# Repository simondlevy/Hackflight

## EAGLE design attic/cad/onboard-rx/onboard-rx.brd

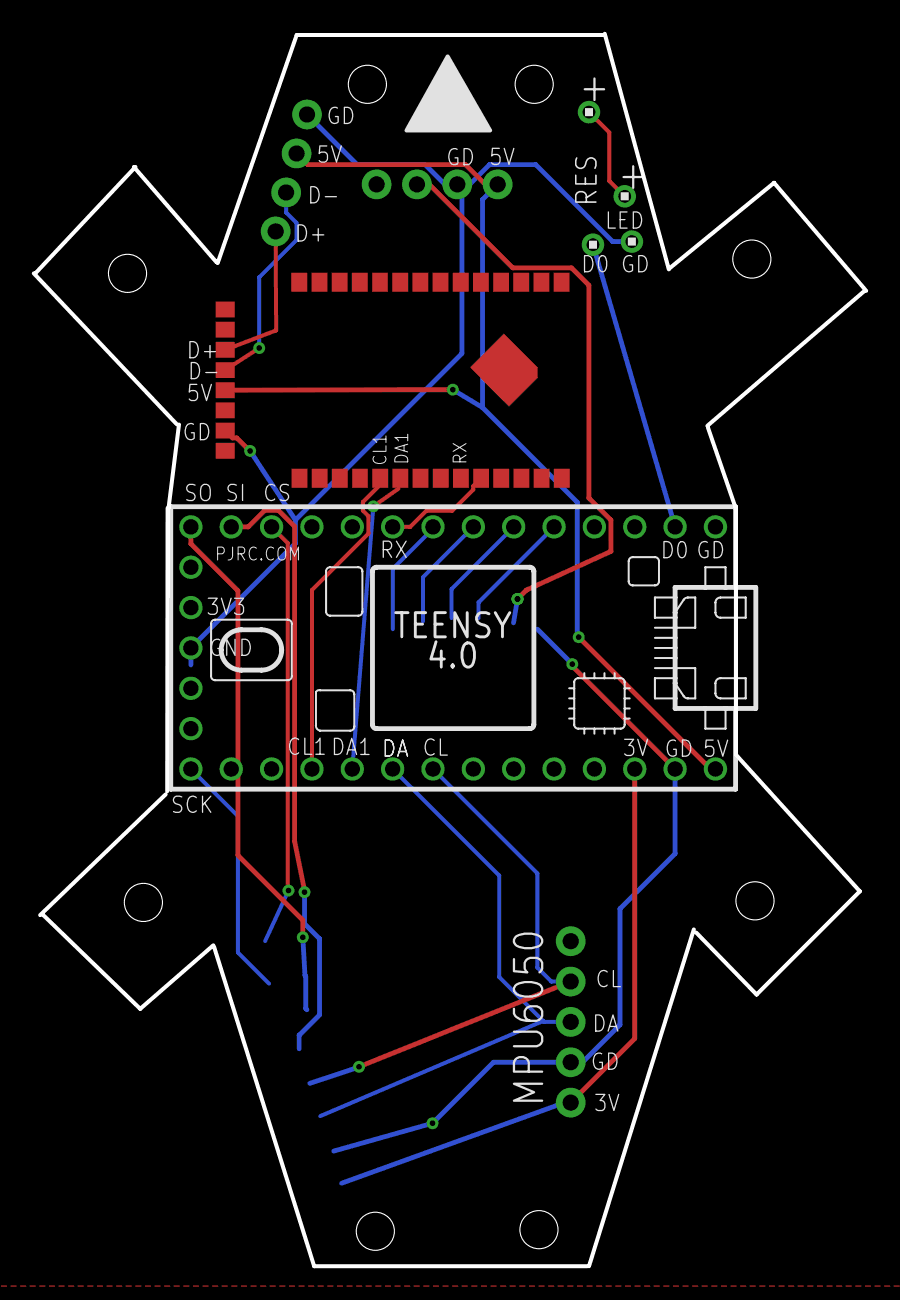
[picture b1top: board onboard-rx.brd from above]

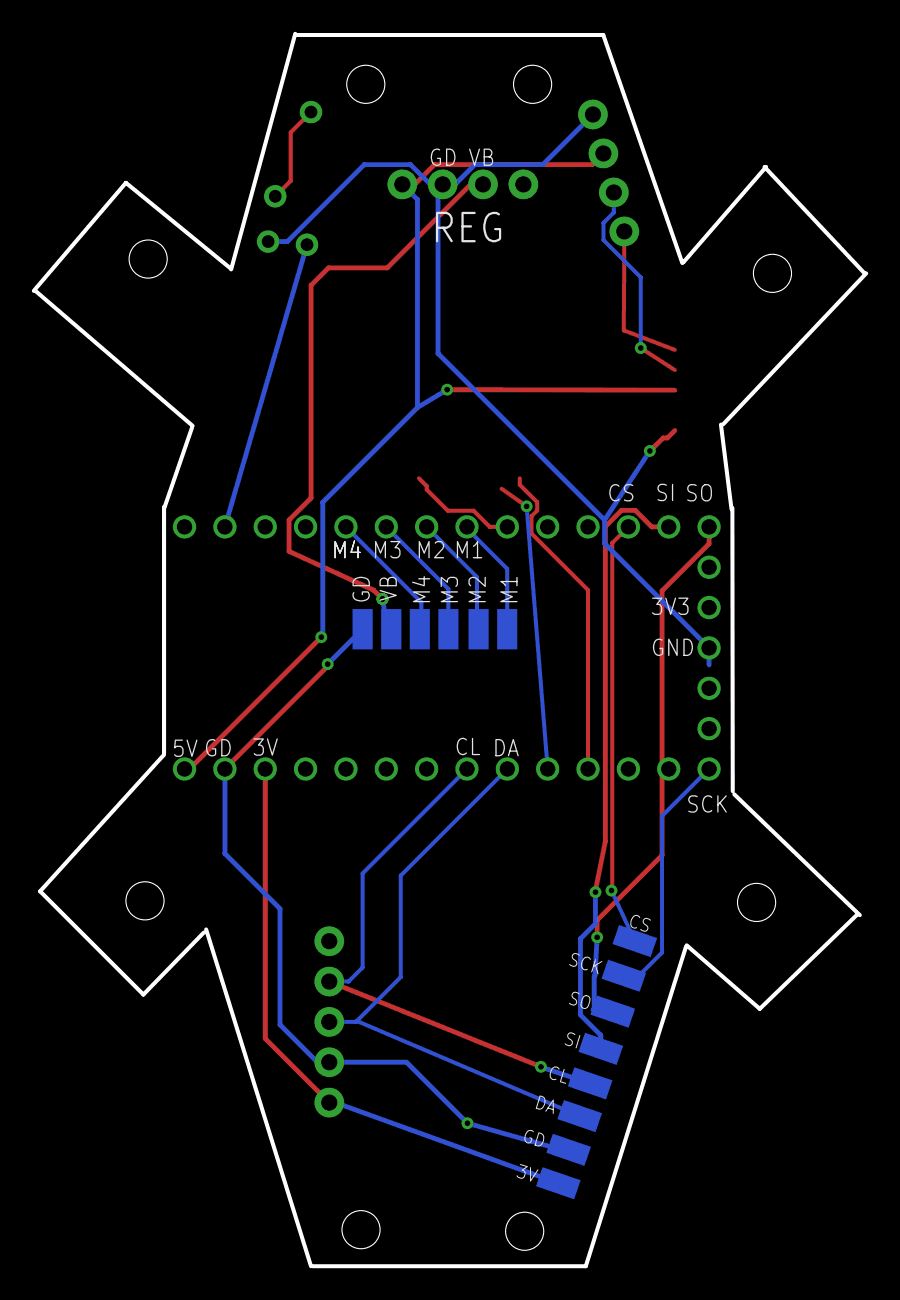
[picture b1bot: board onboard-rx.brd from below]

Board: 2 copper layers, 52.4 x 77.6 mm, 23 parts (14 on the bottom side), 21 nets.

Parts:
3V2, 3V3: SMD1,27-2,54
CS: SMD1,27-2,54
GD1, GD2: SMD1,27-2,54
GND: SMD1,27-2,54
J1: 1X05_NO_SILK
J2: 1X04_NO_SILK
M1, M2, M3, M4: SMD1,27-2,54
REG: 1X04_NO_SILK
RX1, RX2: SMD1,27-2,54
SCK: SMD1,27-2,54
U$1: TEENSY_4.0
U$2: TINYPICO-NANO-CONNECTOR
U$3, U$4, U$6, U$7: 1X1
VBAT: SMD1,27-2,54

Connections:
3V3: 3V2.1, J1.1, U$1.3V3_LO, U$2.3V3
5V: J2.2, REG.1, U$1.VIN, U$2.5V
CS: CS.1, U$1.10/CS
D+: J2.4, U$2.D+
D-: J2.3, U$2.D-
GND: GD1.1, GND.1, J1.2, J2.1, REG.2, U$1.GND2, U$1.GND3, U$2.GND$1, U$2.GND$2, U$2.GND$3, U$2.GND$4, U$7.1
LED_R_IN: U$1.0/RX, U$3.1
LED_R_OUT: U$4.1, U$6.1
M1: M1.1, U$1.6
M2: M2.1, U$1.5
M3: M3.1, U$1.4/CANRX
M4: M4.1, U$1.3/CANTX
MISO: 3V3.1, U$1.12/MISO
MOSI: RX2.1, U$1.11/MOSI
RX: U$1.7, U$2.TX
SCK: SCK.1, U$1.13/SCK
SCL: GD2.1, J1.4, U$1.19/A5/SCL
SCL1: U$1.16/A2, U$2.IO22
SDA: J1.3, RX1.1, U$1.18/A4/SDA
SDA1: U$1.17/A3, U$2.IO21
VB: REG.3, U$2.VBAT, VBAT.1

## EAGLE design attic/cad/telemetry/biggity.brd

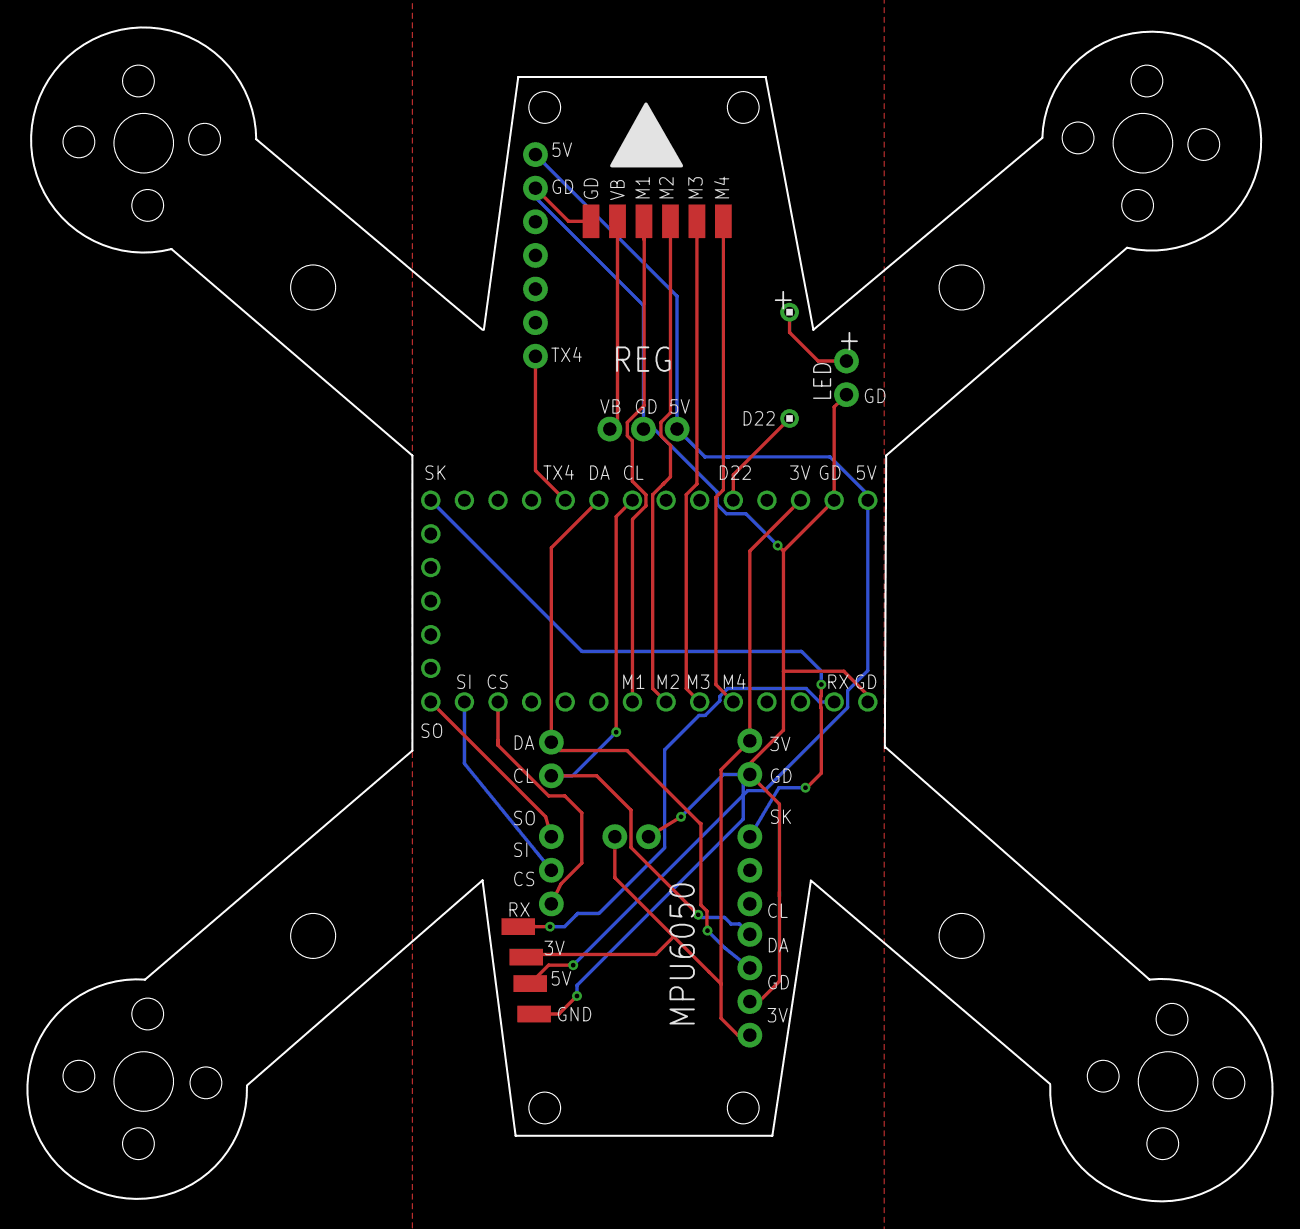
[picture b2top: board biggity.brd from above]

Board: 2 copper layers, 94.1 x 88.7 mm, 22 parts (1 on the bottom side), 18 nets.

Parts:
3V, 5V: SMD1,27-2,54
GND: SMD1,27-2,54
LED: 1X02_NO_SILK
LED_R_IN: 1X1
LED_R_OUT: 1X1
MPU6050: 1X04_NO_SILK
PAD1, PAD2, PAD3, PAD4, PAD5, PAD6: SMD1,27-2,54
PMW3901_1, PMW3901_2: 1X03_NO_SILK
PMW3901_3: 1X02_NO_SILK
REG: 1X03_NO_SILK
RX: SMD1,27-2,54
U$1: TEENSY_4.0
VL53L1_1, VL53L1_2: 1X02_NO_SILK
XIAO_ESP32C6: 1X07_NO_SILK

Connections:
3V3: 3V.1, MPU6050.1, PMW3901_3.1, U$1.3V3_LO, VL53L1_1.2
5V: 5V.1, REG.1, U$1.VIN, XIAO_ESP32C6.7
CS: PMW3901_2.3, U$1.10/CS
GND: GND.1, LED.1, MPU6050.2, PAD1.1, PMW3901_3.2, REG.2, U$1.GND, U$1.GND2, VL53L1_1.1, XIAO_ESP32C6.6
LED_R_IN: LED_R_IN.1, U$1.22/A8
LED_R_OUT: LED.2, LED_R_OUT.1
M1: PAD3.1, U$1.6
M2: PAD4.1, U$1.5
M3: PAD5.1, U$1.4/CANRX
M4: PAD6.1, U$1.3/CANTX
MISO: PMW3901_2.1, U$1.12/MISO
MOSI: PMW3901_2.2, U$1.11/MOSI
RX: RX.1, U$1.0/RX
SCK: PMW3901_1.1, U$1.13/SCK
SCL: MPU6050.4, U$1.19/A5/SCL, VL53L1_2.1
SDA: MPU6050.3, U$1.18/A4/SDA, VL53L1_2.2
TX4: U$1.17/A3, XIAO_ESP32C6.1
VBAT: PAD2.1, REG.3

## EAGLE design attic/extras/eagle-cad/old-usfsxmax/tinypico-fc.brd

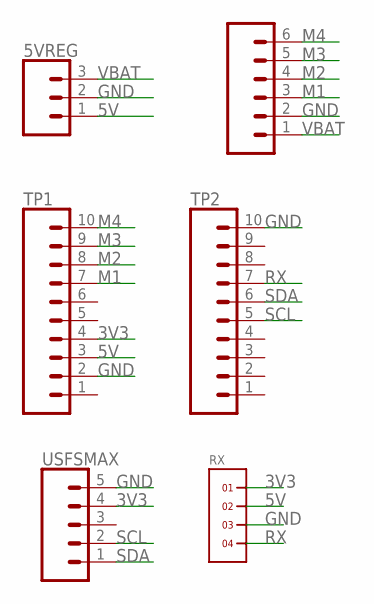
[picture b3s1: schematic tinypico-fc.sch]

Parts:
5VREG: CONN_031X03_NO_SILK; 1X03_NO_SILK
ESC: CONN_06NO_SILK_FEMALE_PTH; 1X06_NO_SILK
RX: 1X4
TP1, TP2: CONN_10NO_SILK_PTH_FEMALE; 1X10_NO_SILK
USFSMAX: CONN_05NO_SILK; 1X05_NO_SILK

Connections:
3V3: RX.1, TP1.4, USFSMAX.4
5V: 5VREG.1, RX.2, TP1.3
GND: 5VREG.2, ESC.2, RX.3, TP1.2, TP2.10, USFSMAX.5
M1: ESC.3, TP1.7
M2: ESC.4, TP1.8
M3: ESC.5, TP1.9
M4: ESC.6, TP1.10
RX: RX.4, TP2.7
SCL: TP2.5, USFSMAX.2
SDA: TP2.6, USFSMAX.1
VBAT: 5VREG.3, ESC.1

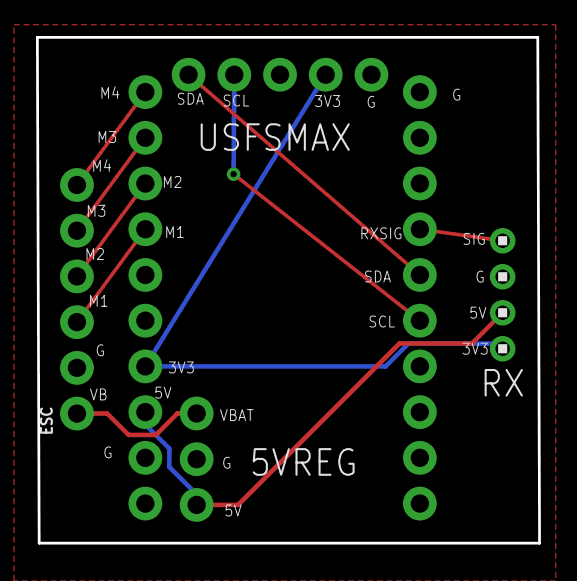
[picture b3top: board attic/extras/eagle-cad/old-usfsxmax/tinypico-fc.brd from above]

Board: 2 copper layers, 27.9 x 28.1 mm, 6 parts (0 on the bottom side), 11 nets.

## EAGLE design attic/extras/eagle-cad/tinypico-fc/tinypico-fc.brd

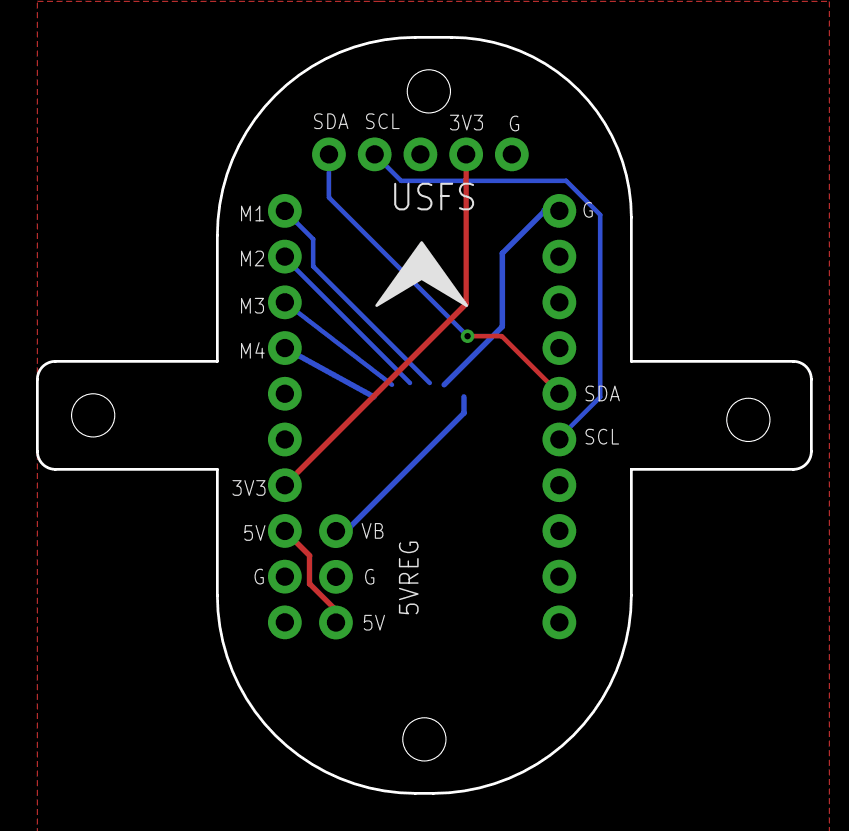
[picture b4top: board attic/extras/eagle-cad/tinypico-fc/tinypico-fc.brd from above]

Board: 2 copper layers, 43.0 x 42.0 mm, 5 parts (1 on the bottom side), 10 nets.

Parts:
5VREG: 1X03_NO_SILK
ESC: BM06B-SRSS-TB; JST-6-SMD-HORI-1.0MM
TP1, TP2: 1X10_NO_SILK
USFS: 1X05_NO_SILK

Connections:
3V3: TP1.4, USFS.4
5V: 5VREG.1, TP1.3
GND: 5VREG.2, ESC.5, TP1.2, TP2.10, USFS.5
M1: ESC.4, TP1.10
M2: ESC.3, TP1.9
M3: ESC.2, TP1.8
M4: ESC.1, TP1.7
SCL: TP2.5, USFS.2
SDA: TP2.6, USFS.1
VBAT: 5VREG.3, ESC.6

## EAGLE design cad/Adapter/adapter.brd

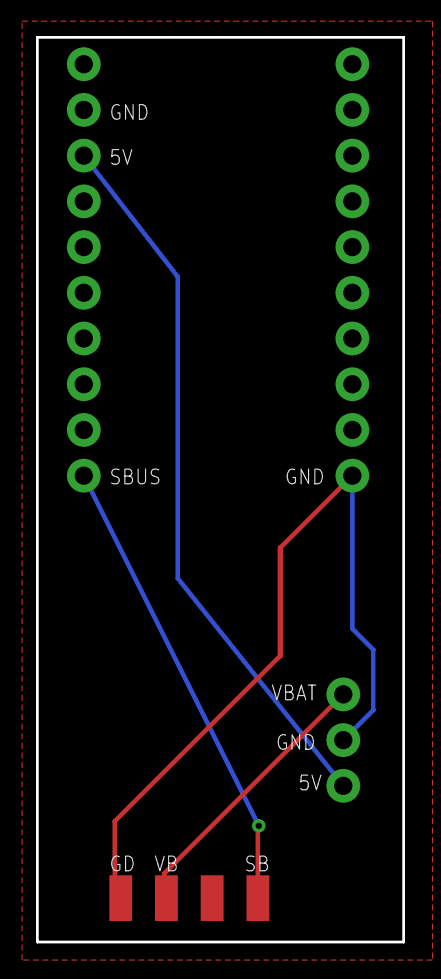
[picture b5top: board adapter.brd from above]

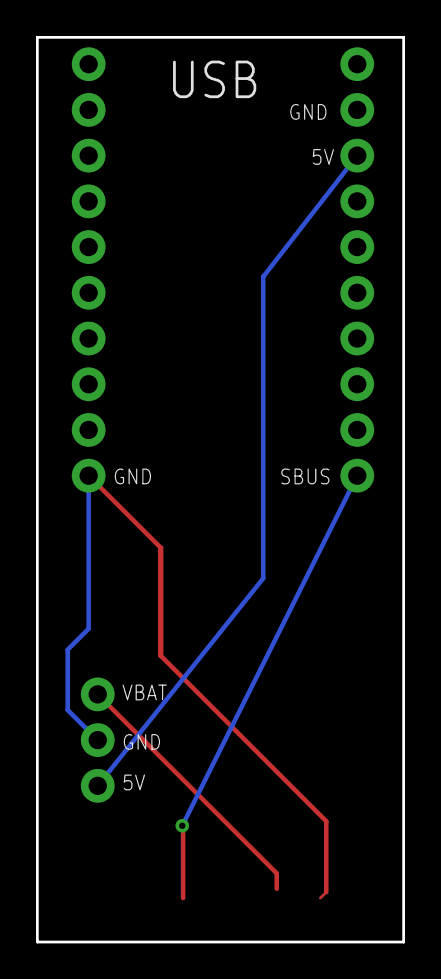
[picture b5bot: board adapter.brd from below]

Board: 2 copper layers, 20.4 x 50.3 mm, 7 parts (2 on the bottom side), 4 nets.

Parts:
GND: SMD1,27-2,54
J1, J2: 1X10_NO_SILK
J3: 1X03_NO_SILK
PAD1: SMD1,27-2,54
SBUS: SMD1,27-2,54
VBAT: SMD1,27-2,54

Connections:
5V: J2.8, J3.1
GND: GND.1, J1.1, J2.9, J3.2
SBUS: J2.1, SBUS.1
VBAT: J3.3, VBAT.1

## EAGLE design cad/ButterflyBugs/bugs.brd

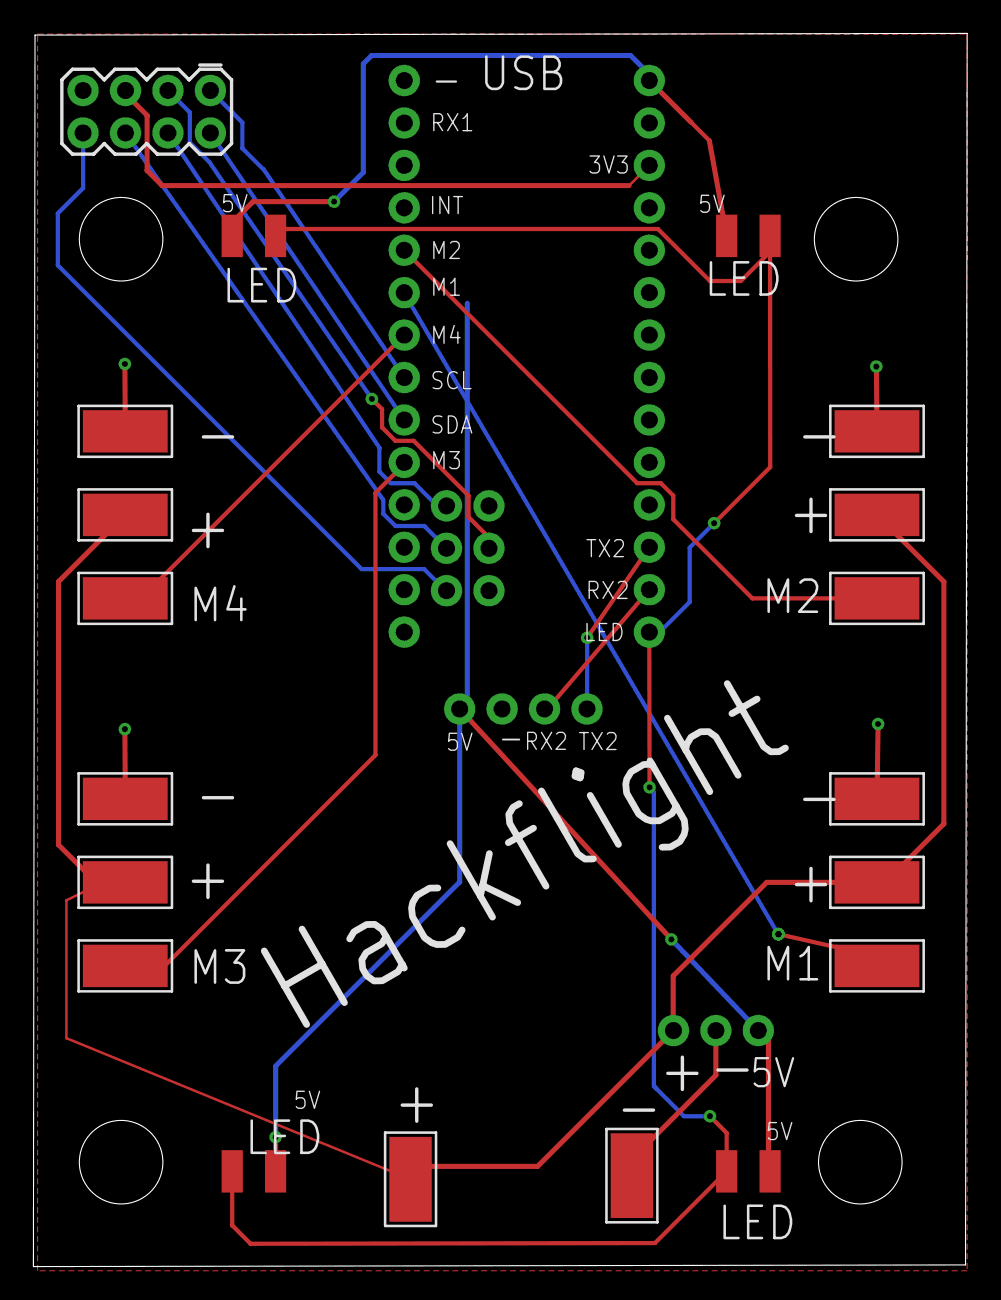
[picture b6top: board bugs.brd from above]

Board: 2 copper layers, 55.9 x 73.8 mm, 28 parts (0 on the bottom side), 17 nets.

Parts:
GND, GND1, GND2, GND3, GND4: WIREPADSMD5-2,5; 5-2,5
J1: 2X3-NS
J3: 2X4
J6, J7: 1X14_NO_SILK
M1, M2, M3, M4: WIREPADSMD5-2,5; 5-2,5
PAD1, PAD2, PAD3, PAD4, PAD5, PAD6, PAD7, PAD8: SMD1,27-2,54
REG: REG; 1X03_NO_SILK
SMIRF: SMIRF; 1X04_NO_SILK
VBAT, VBAT1, VBAT2, VBAT3, VBAT4: WIREPADSMD5-2,5; 5-2,5

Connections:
3V3: J1.5, J3.5, J6.3
5V: J6.1, PAD1.1, PAD3.1, PAD5.1, PAD7.1, REG.1, SMIRF.4
CS1: J1.2, J3.8
GND: GND.1, GND1.1, GND2.1, GND3.1, GND4.1, J1.1, J3.7, J6.2, J7.1, REG.2, SMIRF.3
LED: J6.14, PAD2.1, PAD4.1, PAD6.1, PAD8.1
M1: J7.6, M1.1
M2: J7.5, M2.1
M3: J7.10, M3.1
M4: J7.7, M4.1
MISO1: J1.6, J3.4
MOSI1: J1.3, J3.3
RX2: J6.13, SMIRF.2
SCK1: J1.4, J3.6
SCL: J3.1, J7.8
SDA: J3.2, J7.9
TX2: J6.12, SMIRF.1
VBAT: REG.3, VBAT.1, VBAT1.1, VBAT2.1, VBAT3.1, VBAT4.1

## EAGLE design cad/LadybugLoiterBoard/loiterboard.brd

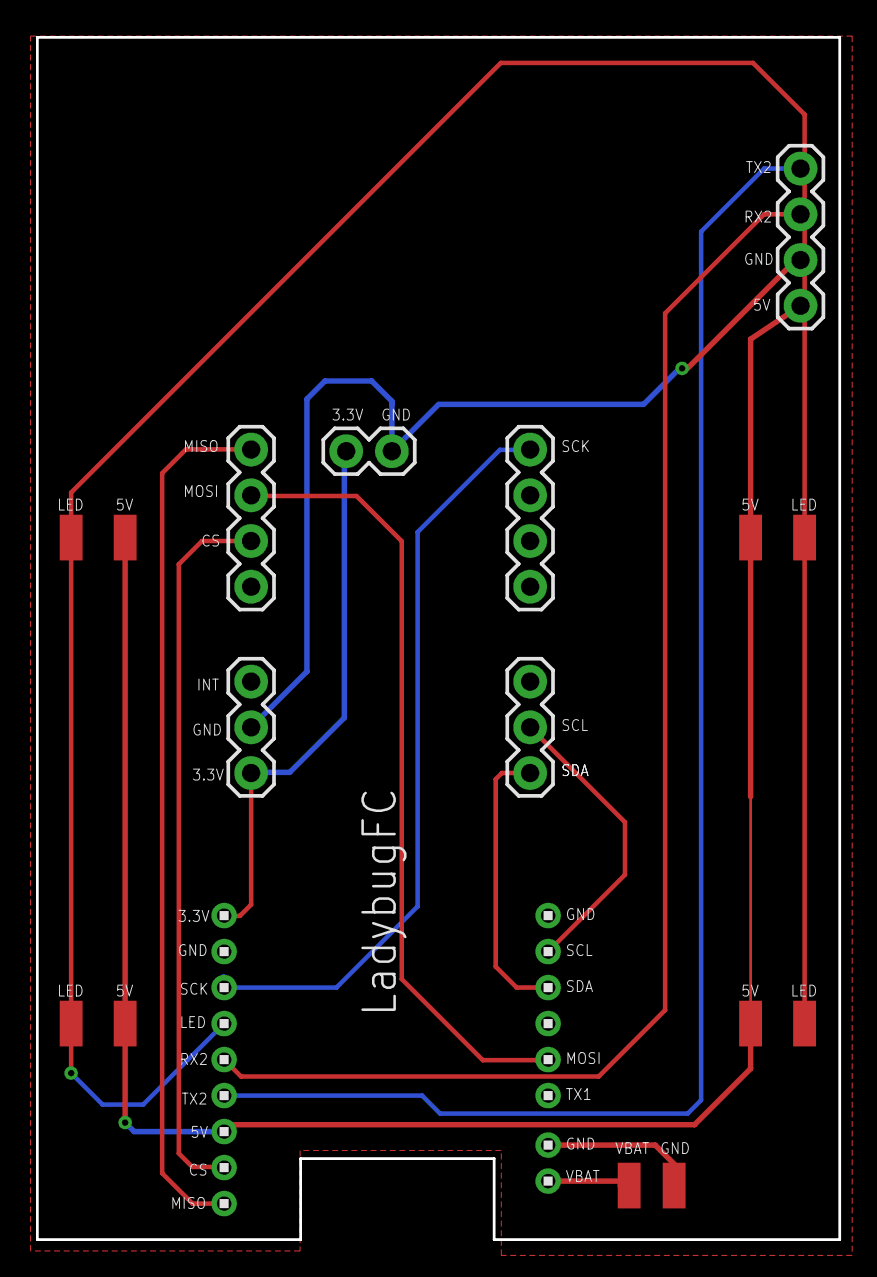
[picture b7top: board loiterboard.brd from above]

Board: 2 copper layers, 44.6 x 66.8 mm, 19 parts (0 on the bottom side), 13 nets.

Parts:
LBLFT: 1X9
LBRGT: 1X6
PAD1, PAD2, PAD3, PAD4, PAD5, PAD7, PAD8, PAD9, PAD10: SMD1,27-2,54
PAD6: LED; SMD1,27-2,54
PMLFT: 1X04
PMRGT: 1X04
PWPWR: 1X02
SMIRF: 1X04
U$1: 1X2
VLLFT: 1X03
VLRGT2: 1X03

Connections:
3.3V: LBLFT.1, PWPWR.1, VLLFT.1
5V: LBLFT.7, PAD1.1, PAD3.1, PAD5.1, PAD7.1, SMIRF.4
A1/SCK: LBLFT.3, PMRGT.4
D4/MISO: LBLFT.9, PMLFT.4
D5/MOSI: LBRGT.5, PMLFT.3
D10/CS: LBLFT.8, PMLFT.2
GND: LBLFT.2, LBRGT.1, PAD10.1, PWPWR.2, SMIRF.3, U$1.1, VLLFT.2
LED: LBLFT.4, PAD2.1, PAD4.1, PAD6.1, PAD8.1
RX2: LBLFT.5, SMIRF.2
SCL: LBRGT.2, VLRGT2.2
SDA: LBRGT.3, VLRGT2.1
TX2: LBLFT.6, SMIRF.1
VBAT: PAD9.1, U$1.2

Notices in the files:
parts and their libraries:
SparkFun-Connectors: Licensing: Creative Commons ShareAlike 4.0 International - https://creativecommons.org/licenses/by-sa/4.0
